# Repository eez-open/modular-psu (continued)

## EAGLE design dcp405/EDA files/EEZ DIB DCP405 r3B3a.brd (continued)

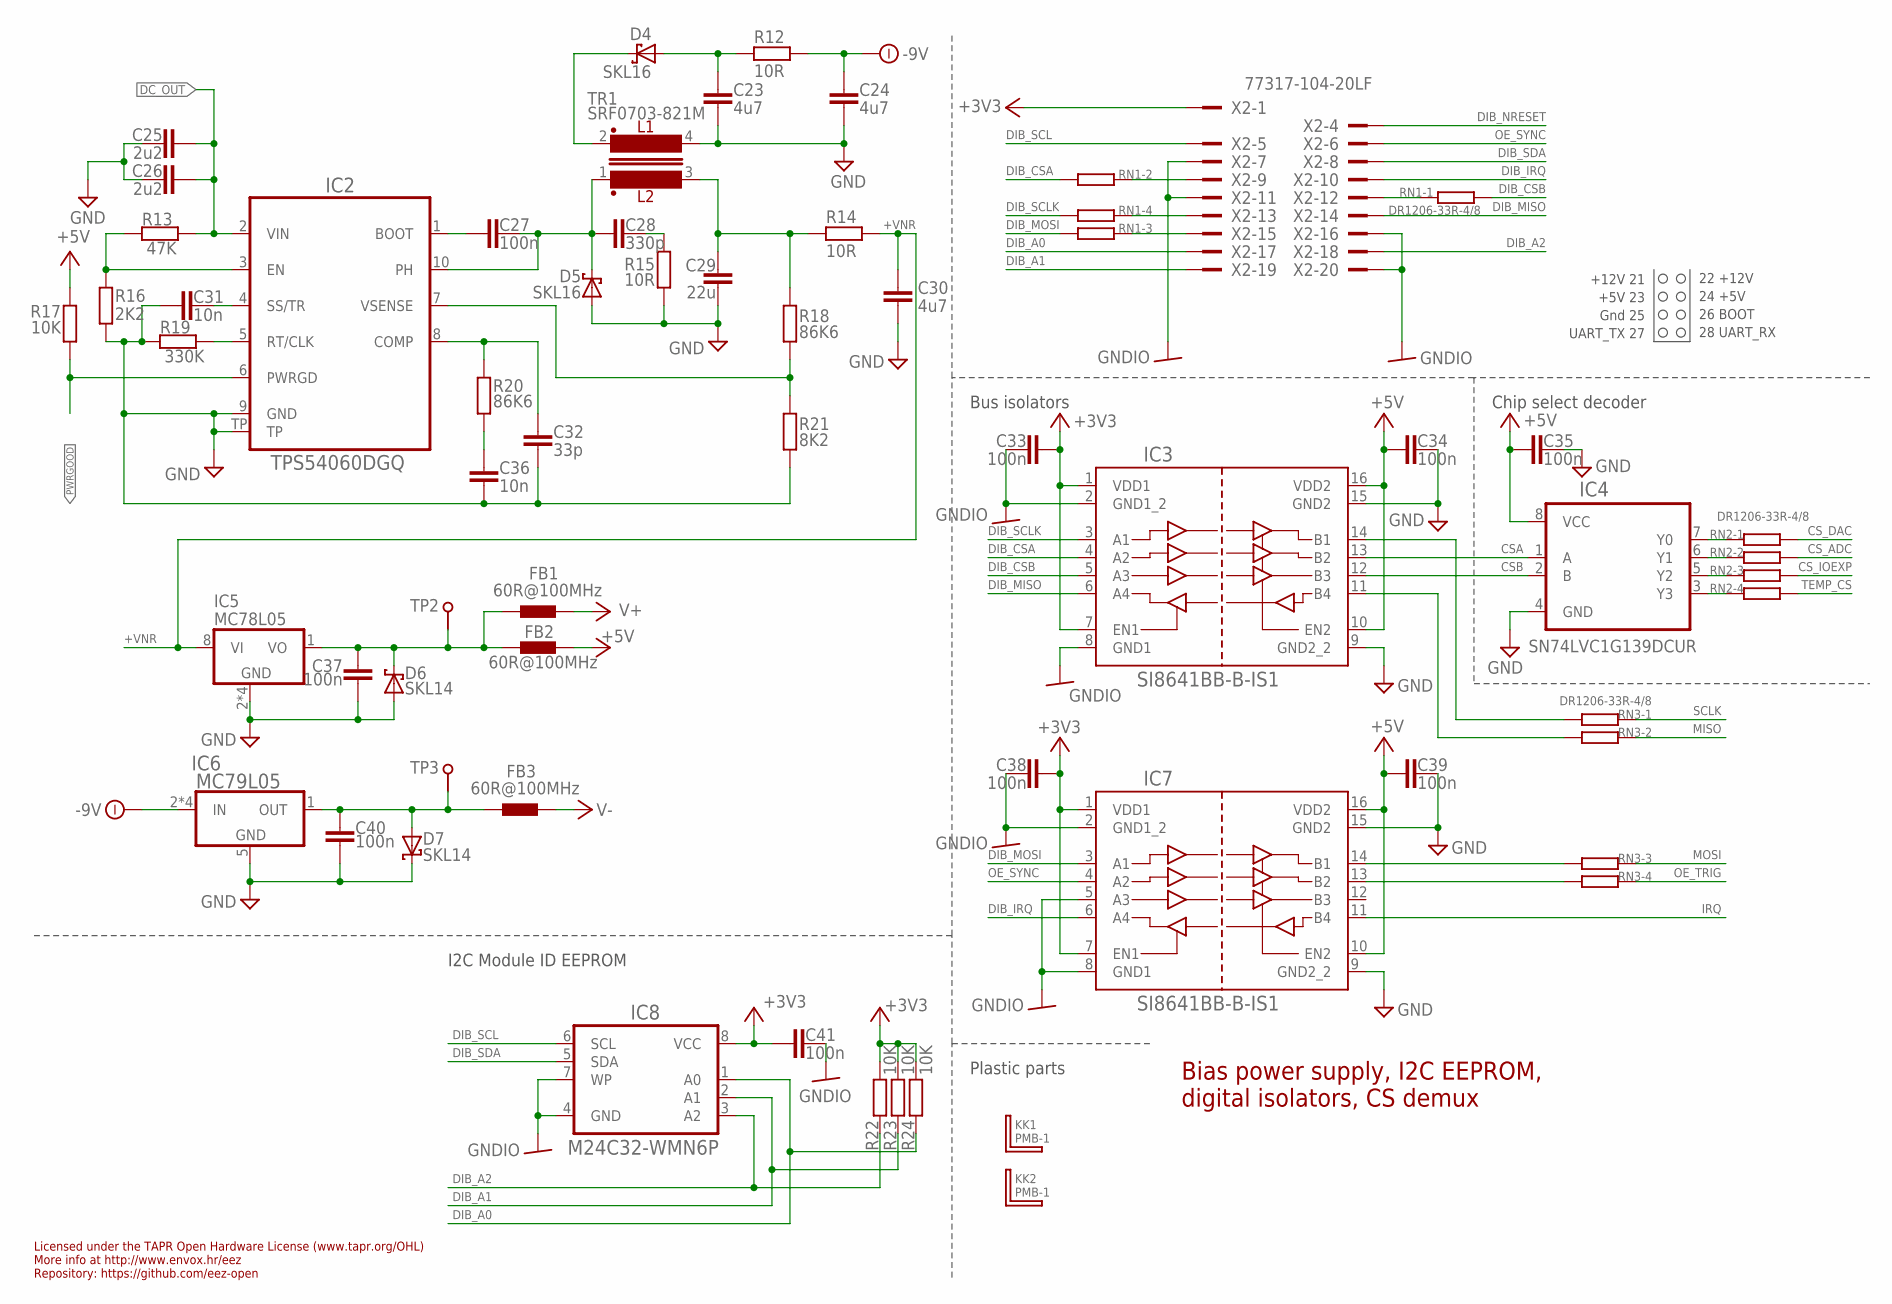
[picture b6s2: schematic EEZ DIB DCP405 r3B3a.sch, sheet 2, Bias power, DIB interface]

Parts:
C23, C24, C30: 4u7; C1206
C25, C26: 2u2; C1206
C27, C33, C34, C35, C37, C38, C39, C40, C41: 100n; C0603
C28: 330p; C0805
C29: 22u; C1210
C31, C36: 10n; C0805
C32: 33p; C0805
D4, D5: SKL16; SOD123
D6, D7: SKL14; SOD123
FB1, FB2, FB3: 60R@100MHz; BEAD0603
IC2: TPS54060DGQ; SOP50P490X110-11N
IC3, IC7: SI8641BB-B-IS1; SOIC-16
IC4: SN74LVC1G139DCUR; DCU8
IC5: MC78L05; SOIC127P600X173-8N
IC6: MC79L05; SOIC127P600X173-8N
IC8: M24C32-WMN6P; SOIC127P600X173-8N
KK1, KK2: PMB-1; PCB-MB
R12, R14, R15: 10R; R1206
R13: 47K; R0805
R16: 2K2; R0805
R17, R22, R23, R24: 10K; R0805
R18, R20: 86K6; R0805
R19: 330K; R0805
R21: 8K2; R0805
RN1, RN2, RN3: DR1206-33R-4/8; CAY16
TP2, TP3: TEST-PIN_0.9MM
TR1: SRF0703-821M; SRF0703
X2: 77317-104-20LF

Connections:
+3V3: C33.1, C38.1, C41.2, IC3.1 (VDD1), IC3.7 (EN1), IC7.1 (VDD1), IC7.7 (EN1), IC8.8 (VCC), R22.1, R23.1, R24.1, X2.1
+5V: C34.2, C35.1, C39.2, FB2.P$2 (2), IC3.10 (EN2), IC3.16 (VDD2), IC4.8 (VCC), IC7.10 (EN2), IC7.16 (VDD2), R17.1; also elsewhere on the board
+5VOUT: C37.1, D6.C, FB1.P$1 (1), FB2.P$1 (1), IC5.1 (VO), TP2.1
+VNR: C30.1, IC5.8 (VI), R14.1; also elsewhere on the board
-9V: C24.1, IC6.2 (IN), IC6.3 (IN), IC6.6 (IN), IC6.7 (IN), R12.1; also elsewhere on the board
CSA: IC3.13 (B2), IC4.1 (A)
CSB: IC3.12 (B3), IC4.2 (B)
CS_ADC: RN2.7 (2); also elsewhere on the board
CS_DAC: RN2.8 (2); also elsewhere on the board
CS_IOEXP: RN2.6 (2); also elsewhere on the board
DC_OUT: C25.1, C26.1, IC2.2 (VIN), R13.2; also elsewhere on the board
DIB_A0: IC8.1 (A0), R24.2, X2.17
DIB_A1: IC8.2 (A1), R23.2, X2.19
DIB_A2: IC8.3 (A2), R22.2, X2.18
DIB_CSA: IC3.4 (A2), RN1.2 (1)
DIB_CSB: IC3.5 (A3), RN1.1
DIB_IRQ: IC7.6 (A4), X2.10
DIB_MISO: IC3.6 (A4), X2.14
DIB_MOSI: IC7.3 (A1), RN1.3 (1)
DIB_NRESET: X2.4
DIB_SCL: IC8.6 (SCL), X2.5
DIB_SCLK: IC3.3 (A1), RN1.4 (1)
DIB_SDA: IC8.5 (SDA), X2.8
GND: C23.2, C24.2, C25.2, C26.2, C29.2, C30.2, C31.2, C32.1, C34.1, C35.2, C36.1, C37.2, C39.1, C40.1, D5.A, D6.A, D7.C, IC2.9 (GND), IC2.TP, IC3.9 (GND2_2), IC3.15 (GND2), IC4.4 (GND), IC5.2 (GND), IC5.3 (GND), IC5.6 (GND), IC5.7 (GND), IC6.5 (GND), IC7.9 (GND2_2), IC7.15 (GND2), R15.1, R16.1, R19.1, R21.1, TR1.4; also elsewhere on the board
GNDIO: C33.2, C38.2, C41.1, IC3.2 (GND1_2), IC3.8 (GND1), IC7.2 (GND1_2), IC7.5 (A3), IC7.8 (GND1), IC8.4 (GND), IC8.7 (WP), X2.7, X2.11, X2.16, X2.20
IRQ: IC7.11 (B4); also elsewhere on the board
MISO: RN3.7 (2); also elsewhere on the board
MOSI: RN3.6 (2); also elsewhere on the board
unnamed: IC7.13 (B2), RN3.4 (1)
unnamed: IC4.5 (Y2), RN2.3 (1)
unnamed: IC4.7 (Y0), RN2.1
unnamed: IC3.11 (B4), RN3.2 (1)
unnamed: RN1.7 (2), X2.9
unnamed: IC4.6 (Y1), RN2.2 (1)
unnamed: RN1.5 (2), X2.13
unnamed: C28.2, R15.2
unnamed: RN1.6 (2), X2.15
unnamed: C40.2, D7.A, FB3.P$1 (1), IC6.1 (OUT), TP3.1
unnamed: RN1.8 (2), X2.12
unnamed: IC2.3 (EN), R13.1, R16.2
unnamed: C31.1, IC2.4 (SS/TR)
unnamed: IC2.5 (RT/CLK), R19.2
unnamed: C32.2, IC2.8 (COMP), R20.2
unnamed: C36.2, R20.1
unnamed: IC4.3 (Y3), RN2.4 (1)
unnamed: C27.2, IC2.1 (BOOT)
unnamed: IC7.14 (B1), RN3.3 (1)
unnamed: IC2.7 (VSENSE), R18.1, R21.2
unnamed: IC3.14 (B1), RN3.1
unnamed: C23.1, D4.A, R12.2
OE_SYNC: IC7.4 (A2), X2.6
OE_TRIG: RN3.5 (2); also elsewhere on the board
PH: C27.1, C28.1, D5.C, IC2.10 (PH), TR1.1
PWRGOOD: IC2.6 (PWRGD), R17.2; also elsewhere on the board
SCLK: RN3.8 (2); also elsewhere on the board
TEMP_CS: RN2.5 (2); also elsewhere on the board
V+: FB1.P$2 (2); also elsewhere on the board
V-: FB3.P$2 (2); also elsewhere on the board
VOUT+: C29.1, R14.2, R18.2, TR1.3
VOUT-: D4.C, TR1.2

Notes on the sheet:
Licensed under the TAPR Open Hardware License (www.tapr.org/OHL)
Repository: https://github.com/eez-open
More info at http://www.envox.hr/eez
I2C Module ID EEPROM
Bus isolators
Bias power supply, I2C EEPROM, digital isolators, CS demux
Plastic parts
Chip select decoder
22 +12V
24 +5V
+5V 23
Gnd 25
+12V 21
26 BOOT
UART_TX 27
28 UART_RX

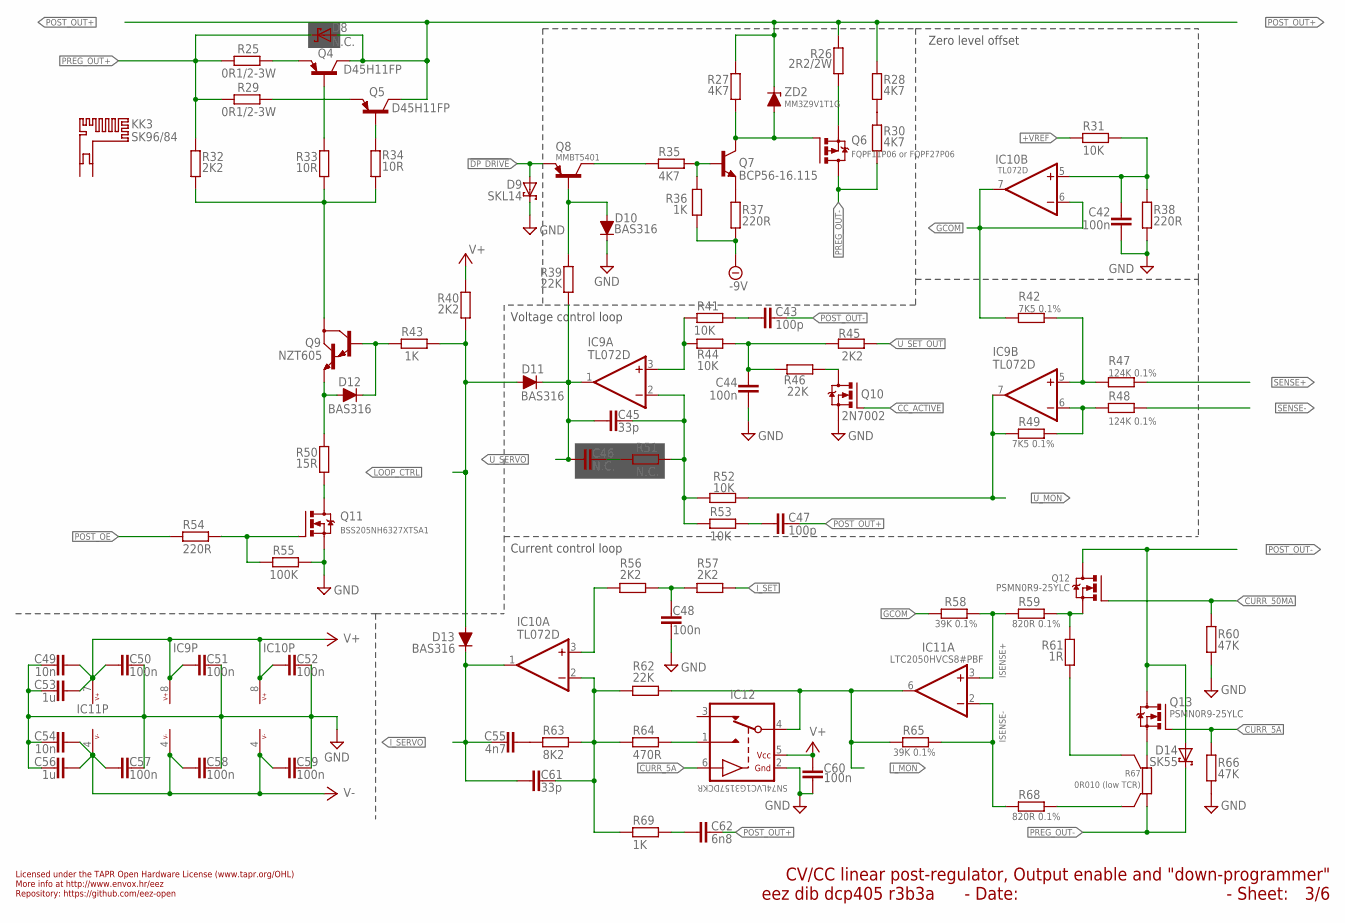
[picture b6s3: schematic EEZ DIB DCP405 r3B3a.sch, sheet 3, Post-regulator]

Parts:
C42, C44, C48, C50, C51, C52, C57, C58, C59, C60: 100n; C0603
C43, C47: 100p; C0805
C45, C61: 33p; C0805
C46: N.C.; C0805
C49, C54: 10n; C0805
C53, C56: 1u; C0805
C55: 4n7; C0805
C62: 6n8; C0805
D8: N.C.; SOD123
D9: SKL14; SOD123
D10, D11, D12, D13: BAS316; SOD323-R
D14: SK55; SMB
IC9, IC10: TL072D; SOIC127P600X173-8N
IC11: LTC2050HVCS8#PBF; SOIC127P600X173-8N
IC12: SN74LVC1G3157DCKR; SOT65P210X110-6N
KK3: SK96/84
Q4, Q5: D45H11FP; TO220FP-V
Q6: FQPF11P06 or FQPF27P06; TO220FP-V
Q7: BCP56-16.115; SOT230P700X180-4N
Q8: MMBT5401; SOT23-BEC
Q9: NZT605; SOT230P700X180-4N
Q10: 2N7002; SOT103P240X110-3N
Q11: BSS205NH6327XTSA1; SOT103P240X110-3N; MPN 2N7002-7-F
Q12, Q13: PSMN0R9-25YLC; SOT669
R25, R29: 0R1/2-3W; R2512
R26: 2R2/2W; R2512
R27, R28, R30, R35: 4K7; R0805
R31, R41, R44, R52, R53: 10K; R0805
R32, R40, R45, R56, R57: 2K2; R0805
R33, R34: 10R; R1206
R36, R43, R69: 1K; R0805
R37, R38, R54: 220R; R0805
R39, R46, R62: 22K; R0805
R42, R49: 7K5 0.1%; R0805
R47, R48: 124K 0.1%; R0805
R50: 15R; R2010
R51: N.C.; R0805
R55: 100K; R0805
R58, R65: 39K 0.1%; R0805
R59, R68: 820R 0.1%; R0805
R60, R66: 47K; R0805
R61: 1R; R1206
R63: 8K2; R0805
R64: 470R; R0805
R67: 0R010 (low TCR); R_2512-4WIRE
ZD2: MM3Z9V1T1G; SOD323-R

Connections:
5A_S: Q13.1 (S), Q13.2 (S), Q13.3 (S), R67.2
50MA_S: Q12.1 (S), Q12.2 (S), Q12.3 (S), R59.1, R61.1
!DP_DRIVE: D9.A, Q8.E; also elsewhere on the board
+VREF: R31.1; also elsewhere on the board
-9V: R36.2, R37.2; also elsewhere on the board
CC_ACTIVE: Q10.1 (G); also elsewhere on the board
CURR_5A: IC12.6 (CTRL), Q13.4 (G), R66.2; also elsewhere on the board
CURR_50MA: Q12.4 (G), R60.2; also elsewhere on the board
DARL_C1: Q9.2 (C), Q9.4 (C), R32.1, R33.1, R34.1
DP_S: Q6.3 (S), R26.1
GCOM: IC10.6 (-IN), IC10.7 (OUT), R42.1, R58.1
GND: C42.2, C44.2, C48.2, C49.1, C50.2, C51.1, C52.1, C53.1, C54.1, C56.1, C57.2, C58.1, C59.1, C60.2, D9.C, D10.C, IC12.2 (GND), Q10.2 (S), Q11.2 (S), R38.2, R55.1, R60.1, R66.1; also elsewhere on the board
ISENSE+: IC11.3 (+IN), R58.2, R59.2
ISENSE-: IC11.2 (-IN), R65.1, R68.2
I_MON: IC11.6 (OUT), IC12.4 (COM), R62.1, R65.2; also elsewhere on the board
I_SERVO: C55.2, C61.2, D13.C, IC10.1 (OUT); also elsewhere on the board
I_SET: R57.1; also elsewhere on the board
LOOP_CTRL: D11.A, D13.A, R40.1, R43.1; also elsewhere on the board
unnamed: Q10.3 (D), R46.1
unnamed: C48.1, R56.1, R57.2
unnamed: R61.2, R67.2S
unnamed: C46.1, R51.2
unnamed: C55.1, R63.1
unnamed: Q5.1 (B), R34.2
unnamed: IC12.1 (NO), R64.1
unnamed: IC10.3 (+IN), R56.2
unnamed: IC9.3 (+IN), R41.2, R44.2
unnamed: C45.1, IC9.2 (-IN), R51.1, R52.2, R53.2
unnamed: Q4.1 (B), R33.2
unnamed: D12.A, Q9.3 (E), R50.2
unnamed: Q11.3 (D), R50.1
unnamed: C62.2, R69.1
unnamed: C61.1, IC10.2 (-IN), R62.2, R63.2, R64.2, R69.2
unnamed: C43.2, R41.1
unnamed: C47.2, R53.1
unnamed: R28.1, R30.2
unnamed: Q7.1 (B), R35.1, R36.1
unnamed: Q8.C, R35.2
unnamed: D10.A, Q8.B, R39.2
unnamed: Q11.1 (G), R54.1, R55.2
unnamed: Q7.3 (E), R37.1
unnamed: D12.C, Q9.1 (B), R43.2
unnamed: C42.1, IC10.5 (+IN), R31.2, R38.1
unnamed: IC9.5 (+IN), R42.2, R47.1
unnamed: IC9.6 (-IN), R48.1, R49.2
unnamed: R67.1S, R68.1
PASS_E1: Q4.3 (E), R25.2
PASS_E2: Q5.3 (E), R29.2
POST_OE: R54.2; also elsewhere on the board
POST_OUT+: C47.1, C62.1, D8.A, Q4.2 (C), Q5.2 (C), R26.2, R27.1, R28.2, ZD2.C; also elsewhere on the board
POST_OUT-: C43.1, D14.A, Q12.MB (D), Q13.MB (D); also elsewhere on the board
PREG_OUT+: D8.C, R25.1, R29.1, R32.2; also elsewhere on the board
PREG_OUT-: D14.C, Q6.2 (D), R30.1, R67.1; also elsewhere on the board
Q7C: Q6.1 (G), Q7.2 (C), Q7.4 (C), R27.2, ZD2.A
SENSE+: R47.2; also elsewhere on the board
SENSE-: R48.2; also elsewhere on the board
U_MON: IC9.7 (OUT), R49.1, R52.1; also elsewhere on the board
U_SERVO: C45.2, C46.2, D11.C, IC9.1 (OUT), R39.1; also elsewhere on the board
U_SET_OUT: R45.1; also elsewhere on the board
U_SET_OVP: C44.1, R44.1, R45.2, R46.2
V+: C49.2, C50.1, C51.2, C52.2, C53.2, C60.1, IC9.8 (V+), IC10.8 (V+), IC11.7 (V+), IC12.5 (VDD), R40.2; also elsewhere on the board
V-: C54.2, C56.2, C57.1, C58.2, C59.2, IC9.4 (V-), IC10.4 (V-), IC11.4 (V-); also elsewhere on the board

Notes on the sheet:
Voltage control loop
Licensed under the TAPR Open Hardware License (www.tapr.org/OHL)
Repository: https://github.com/eez-open
More info at http://www.envox.hr/eez
Zero level offset
CV/CC linear post-regulator, Output enable and "down-programmer"
- Sheet:
- Date:
Current control loop

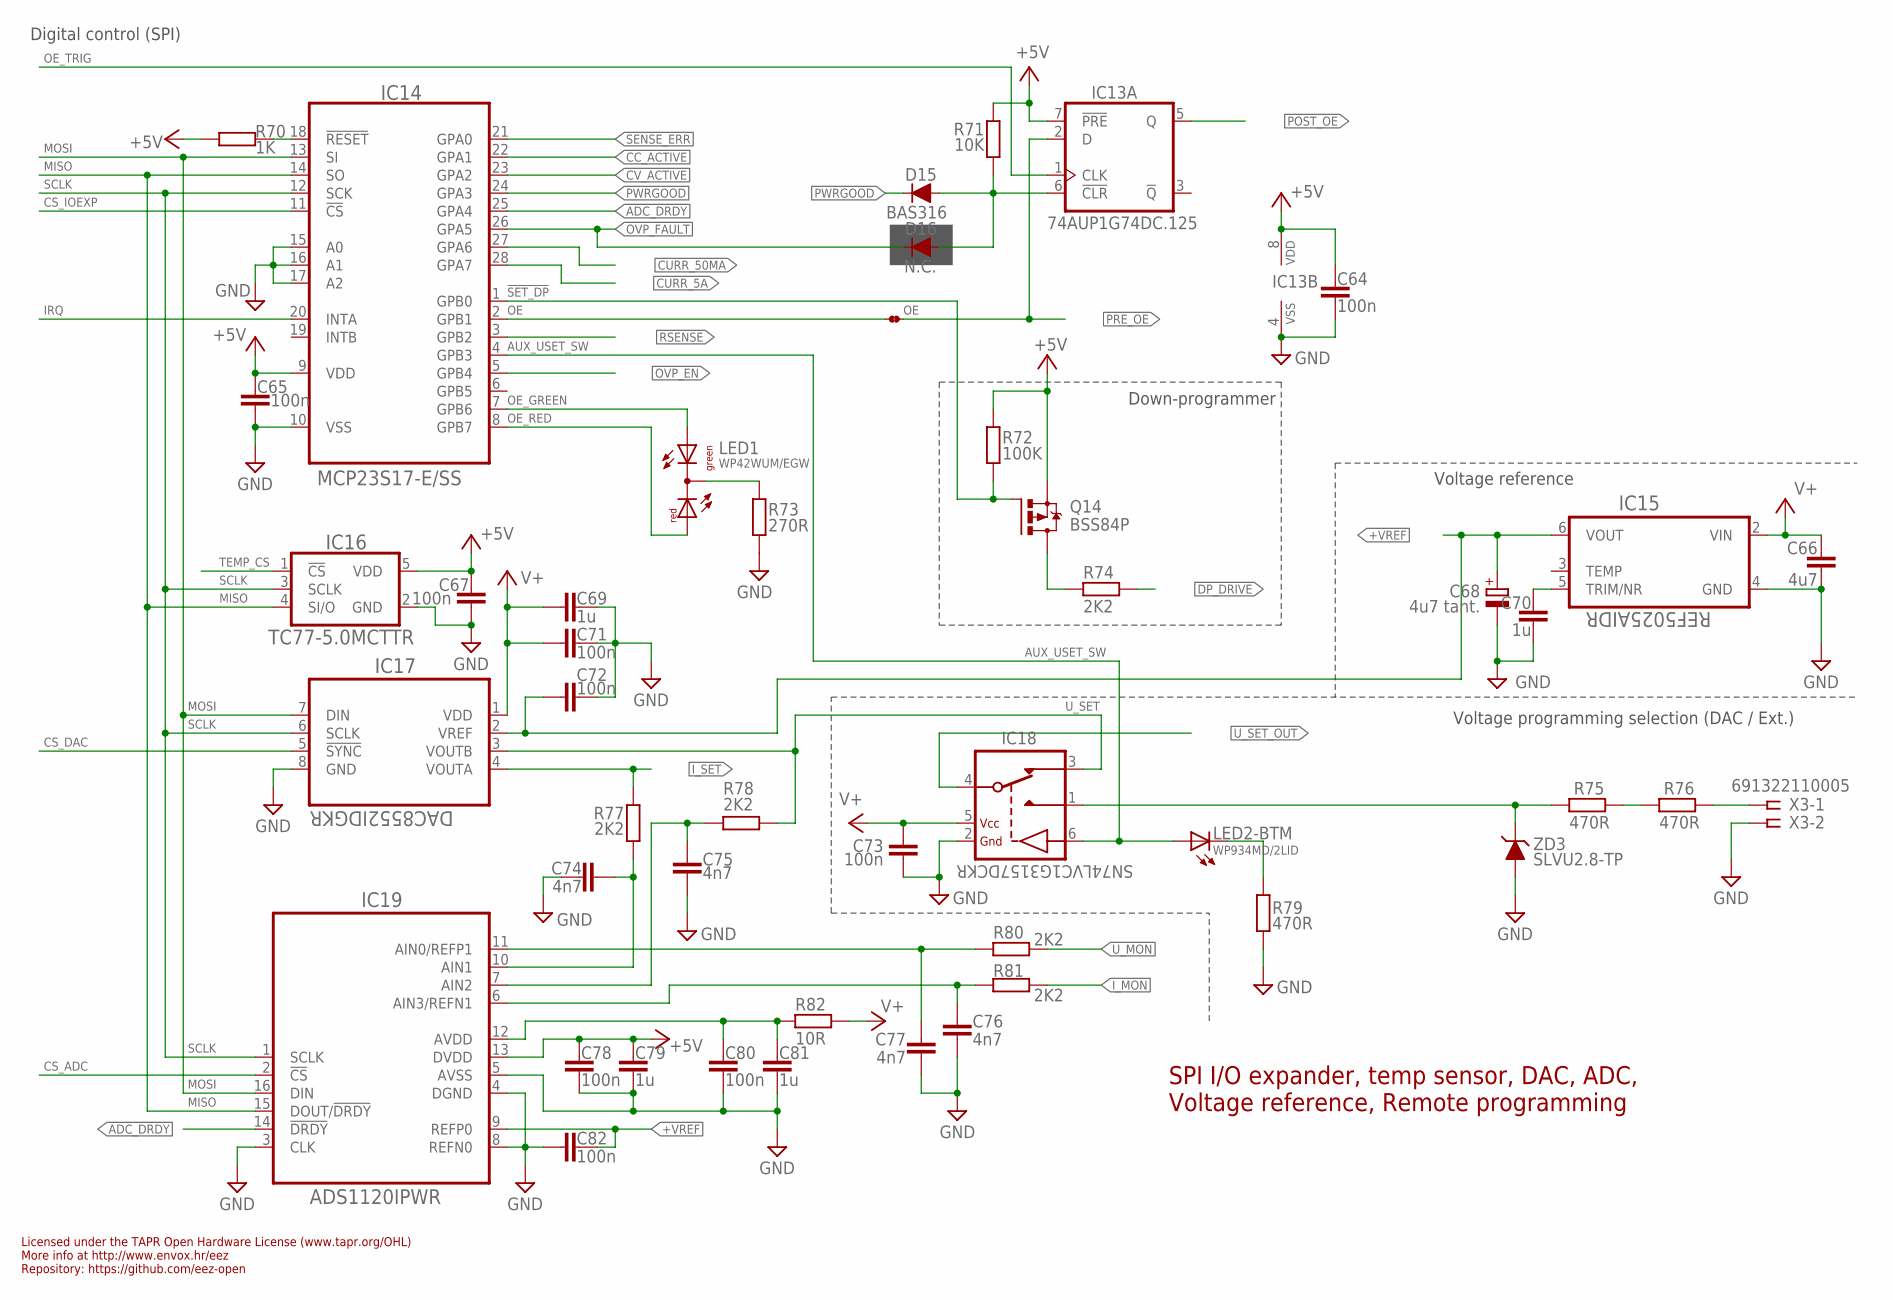
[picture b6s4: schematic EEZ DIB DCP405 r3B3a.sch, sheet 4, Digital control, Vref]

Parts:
C64, C65, C67, C71, C72, C73, C78, C80, C82: 100n; C0603
C66: 4u7; C1206
C68: 4u7 tant.; EC1206
C69, C70, C79, C81: 1u; C0805
C74, C75, C76, C77: 4n7; C0805
D15: BAS316; SOD323-R
D16: N.C.; SOD323-R
IC13: 74AUP1G74DC.125; DCU8
IC14: MCP23S17-E/SS; SOP65P780X200-28N
IC15: REF5025AIDR; SOIC127P600X175-8N
IC16: TC77-5.0MCTTR; SOT23-5
IC17: DAC8552IDGKR; DGK8-M
IC18: SN74LVC1G3157DCKR; SOT65P210X110-6N
IC19: ADS1120IPWR; PW(R-PDSO-G16)
LED1: WP42WUM/EGW; L-42WUM-1EGWT
LED2: WP934MD/2LID; WP934MD
OE: JP2-NOCUT
Q14: BSS84P; SOT95P237X112-3N
R70: 1K; R0805
R71: 10K; R0805
R72: 100K; R0805
R73: 270R; R0805
R74, R77, R78, R80, R81: 2K2; R0805
R75, R76, R79: 470R; R0805
R82: 10R; R1206
X3: 691322110005; MC1,5/5-G-3,5
ZD3: SLVU2.8-TP; SOT23

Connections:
!ADC_DRDY: IC14.25 (GPA4), IC19.14 (!DRDY)
!DP_DRIVE: R74.1; also elsewhere on the board
!IOEXP_RST: IC14.18 (!RESET), R70.2
!OVP_FAULT: D16.C, IC14.26 (GPA5); also elsewhere on the board
!SET_DP: IC14.1 (GPB0), Q14.1 (G), R72.2
+5V: C64.2, C65.1, C67.1, C78.2, C79.2, IC13.7 (!PRE), IC13.8 (VDD), IC14.9 (VDD), IC16.5 (VDD), IC19.13 (DVDD), Q14.2 (S), R70.1, R71.1, R72.1; also elsewhere on the board
+VREF: C68.+, C72.2, C82.2, IC15.6 (VOUT), IC17.2 (VREF), IC19.9 (REFP0); also elsewhere on the board
AUX_IN: IC18.1 (NO), R75.1, ZD3.3 (C)
AUX_USET_SW: IC14.4 (GPB3), IC18.6 (CTRL), LED2.BA (A)
CC_ACTIVE: IC14.22 (GPA1); also elsewhere on the board
CS_ADC: IC19.2 (!CS); also elsewhere on the board
CS_DAC: IC17.5 (!SYNC); also elsewhere on the board
CS_IOEXP: IC14.11 (!CS); also elsewhere on the board
CURR_5A: IC14.28 (GPA7); also elsewhere on the board
CURR_50MA: IC14.27 (GPA6); also elsewhere on the board
CV_ACTIVE: IC14.23 (GPA2); also elsewhere on the board
GND: C64.1, C65.2, C66.2, C67.2, C68.-, C69.2, C70.2, C71.1, C72.1, C73.2, C74.1, C75.1, C76.2, C77.1, C78.1, C79.1, C80.1, C81.1, C82.1, IC13.4 (VSS), IC14.10 (VSS), IC14.15 (A0), IC14.16 (A1), IC14.17 (A2), IC15.4 (GND), IC16.2 (GND), IC17.8 (GND), IC18.2 (GND), IC19.3 (CLK), IC19.4 (DGND), IC19.5 (AVSS), IC19.8 (REFN0), R73.2, R79.1, X3.2, ZD3.1 (A), ZD3.2 (A); also elsewhere on the board
IRQ: IC14.20 (INTA); also elsewhere on the board
I_MON: R81.1; also elsewhere on the board
I_SET: IC17.4 (VOUTA), R77.1; also elsewhere on the board
MISO: IC14.14 (SO), IC16.4 (SI/O), IC19.15 (DOUT/!DRDY); also elsewhere on the board
MOSI: IC14.13 (SI), IC17.7 (DIN), IC19.16 (DIN); also elsewhere on the board
unnamed: LED1.CC (C), R73.1
unnamed: R75.2, R76.1
unnamed: R76.2, X3.1
unnamed: Q14.3 (D), R74.2
unnamed: D15.A, D16.A, IC13.6 (!CLR), R71.2
unnamed: C80.2, C81.2, IC19.12 (AVDD), R82.2
unnamed: C70.1, IC15.5 (TRIM/NR)
unnamed: C74.2, IC19.10 (AIN1), R77.2
unnamed: C77.2, IC19.11 (AIN0/REFP1), R80.2
unnamed: C75.2, IC19.7 (AIN2), R78.2
unnamed: C76.1, IC19.6 (AIN3/REFN1), R81.2
unnamed: LED2.BC (C), R79.2
OE: IC14.2 (GPB1), OE.1
OE_GREEN: IC14.7 (GPB6), LED1.GREEN (AG)
OE_RED: IC14.8 (GPB7), LED1.RED (AR)
OE_TRIG: IC13.1 (CLK); also elsewhere on the board
OVP_EN: IC14.5 (GPB4); also elsewhere on the board
POST_OE: IC13.5 (Q); also elsewhere on the board
PRE_OE: IC13.2 (D), OE.2; also elsewhere on the board
PWRGOOD: D15.C, IC14.24 (GPA3); also elsewhere on the board
RSENSE: IC14.3 (GPB2); also elsewhere on the board
SCLK: IC14.12 (SCK), IC16.3 (SCLK), IC17.6 (SCLK), IC19.1 (SCLK); also elsewhere on the board
SENSE_ERR: IC14.21 (GPA0); also elsewhere on the board
TEMP_CS: IC16.1 (!CS); also elsewhere on the board
U_MON: R80.1; also elsewhere on the board
U_SET: IC17.3 (VOUTB), IC18.3 (NC), R78.1
U_SET_OUT: IC18.4 (COM); also elsewhere on the board
V+: C66.1, C69.1, C71.2, C73.1, IC15.2 (VIN), IC17.1 (VDD), IC18.5 (VDD), R82.1; also elsewhere on the board

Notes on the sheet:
Digital control (SPI)
Voltage reference
Licensed under the TAPR Open Hardware License (www.tapr.org/OHL)
Repository: https://github.com/eez-open
More info at http://www.envox.hr/eez
SPI I/O expander, temp sensor, DAC, ADC, Voltage reference, Remote programming
Voltage programming selection (DAC / Ext.)
Down-programmer

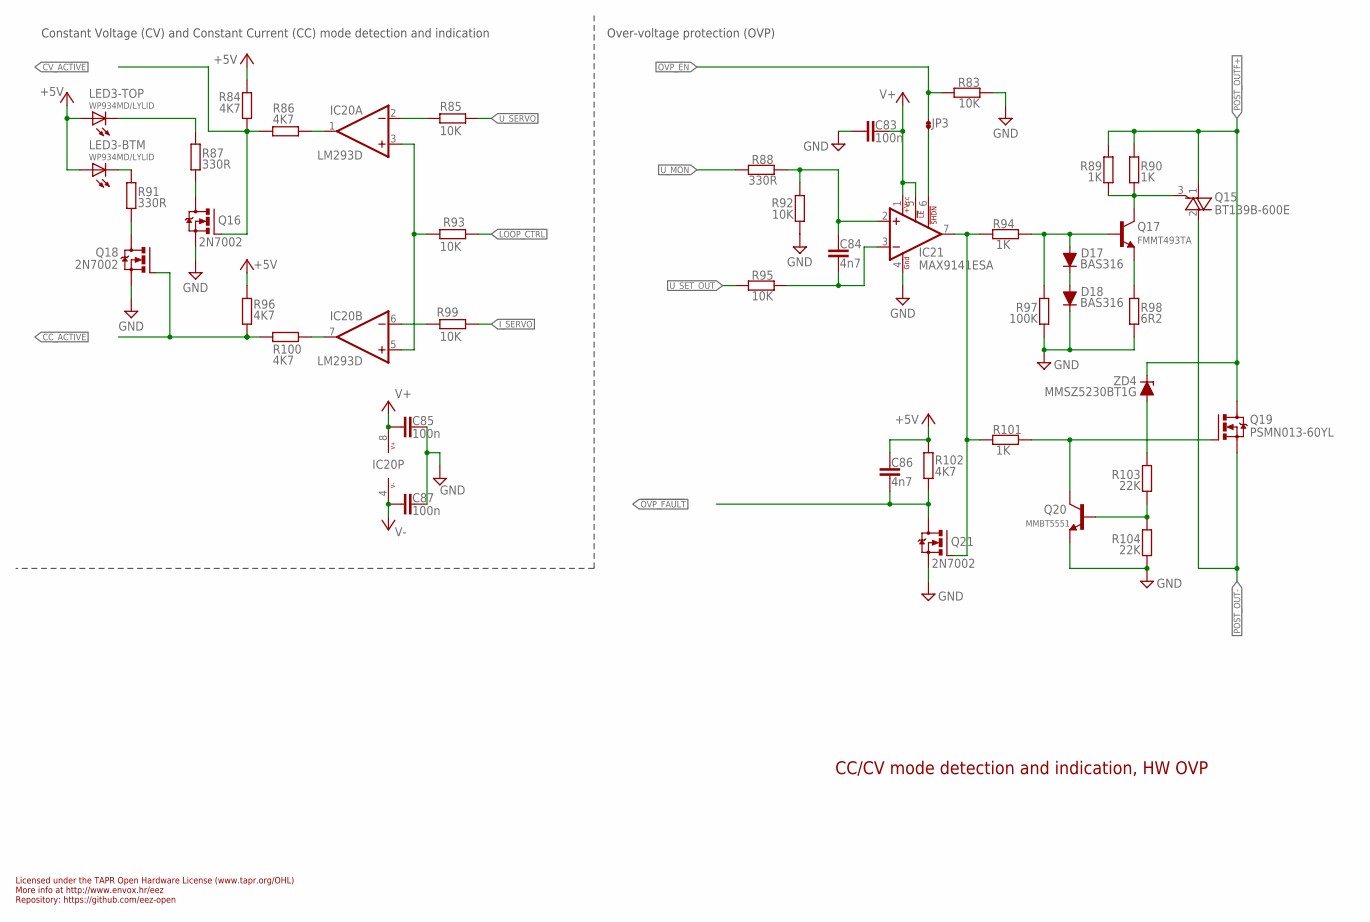
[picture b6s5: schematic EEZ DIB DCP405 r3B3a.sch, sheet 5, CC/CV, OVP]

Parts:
C83, C85, C87: 100n; C0603
C84, C86: 4n7; C0805
D17, D18: BAS316; SOD323-R
IC20: LM293D; SOIC127P600X173-8N
IC21: MAX9141ESA; SOIC127P600X173-8N
JP3: JP2-NOCUT-0805; JP2-0805-NOCUT
LED3: WP934MD/LYLID; WP934MD
Q15: BT139B-600E; D2PAK
Q16, Q18, Q21: 2N7002; SOT103P240X110-3N
Q17: FMMT493TA; SOT23-BEC
Q19: PSMN013-60YL; SOT669
Q20: MMBT5551; SOT23-BEC
R83, R85, R92, R93, R95, R99: 10K; R0805
R84, R86, R96, R100, R102: 4K7; R0805
R87, R88, R91: 330R; R0805
R89, R90, R94, R101: 1K; R0805
R97: 100K; R0805
R98: 6R2; R0805
R103, R104: 22K; R0805
ZD4: MMSZ5230BT1G; SOD123

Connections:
!OVP_FAULT: C86.2, Q21.3 (D), R102.2; also elsewhere on the board
+5V: C86.1, LED3.BA (A), LED3.TA (A), R84.2, R96.2, R102.1; also elsewhere on the board
CC_ACTIVE: Q18.1 (G), R96.1, R100.2; also elsewhere on the board
CC_LED: LED3.BC (C), R91.2
CV_ACTIVE: Q16.1 (G), R84.1, R86.2; also elsewhere on the board
CV_LED: LED3.TC (C), R87.1
D_CC: Q18.3 (D), R91.1
D_CV: Q16.3 (D), R87.2
GND: C83.1, C85.1, C87.1, D18.C, IC21.4 (GND), Q16.2 (S), Q18.2 (S), Q20.E, Q21.2 (S), R83.1, R92.2, R97.1, R98.1, R104.1; also elsewhere on the board
I_SERVO: R99.1; also elsewhere on the board
LOOP_CTRL: R93.2; also elsewhere on the board
unnamed: IC21.6 (!SHDN), JP3.2
unnamed: IC21.7 (OUT), Q21.1 (G), R94.2, R101.2
unnamed: Q15.3 (G), Q17.C, R89.1, R90.1
unnamed: Q17.E, R98.2
unnamed: D17.C, D18.A
unnamed: D17.A, Q17.B, R94.1, R97.2
unnamed: R103.2, ZD4.A
unnamed: Q20.B, R103.1, R104.2
unnamed: Q19.4 (G), Q20.C, R101.1
unnamed: IC20.1 (OUT), R86.1
unnamed: IC20.7 (OUT), R100.1
unnamed: IC20.2 (-IN), R85.2
unnamed: IC20.6 (-IN), R99.2
unnamed: IC20.3 (+IN), IC20.5 (+IN), R93.1
OVP_EN: JP3.1, R83.2; also elsewhere on the board
OVP_IN+: C84.1, IC21.2 (+IN), R88.2, R92.1
OVP_IN-: C84.2, IC21.3 (-IN), R95.2
POST_OUT-: Q15.2 (A2), Q19.1 (S), Q19.2 (S), Q19.3 (S); also elsewhere on the board
POST_OUTF+: Q15.1 (A1), Q19.MB (D), R89.2, R90.2, ZD4.C; also elsewhere on the board
U_MON: R88.1; also elsewhere on the board
U_SERVO: R85.1; also elsewhere on the board
U_SET_OUT: R95.1; also elsewhere on the board
V+: C83.2, C85.2, IC20.8 (V+), IC21.1 (+VCC), IC21.5 (!LE); also elsewhere on the board
V-: C87.2, IC20.4 (V-); also elsewhere on the board

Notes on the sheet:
Licensed under the TAPR Open Hardware License (www.tapr.org/OHL)
Repository: https://github.com/eez-open
More info at http://www.envox.hr/eez
CC/CV mode detection and indication, HW OVP
Constant Voltage (CV) and Constant Current (CC) mode detection and indication
Over-voltage protection (OVP)

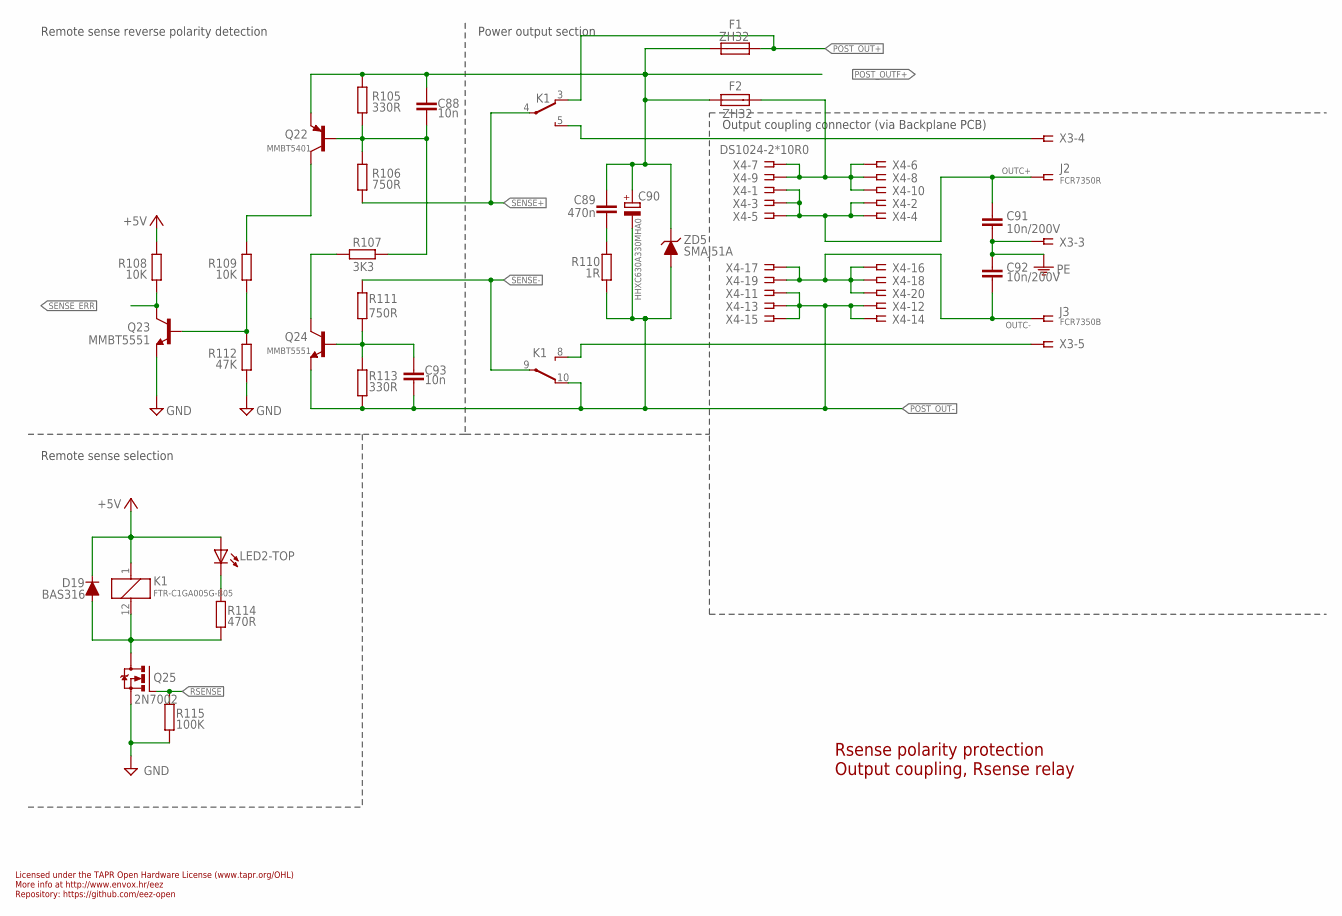
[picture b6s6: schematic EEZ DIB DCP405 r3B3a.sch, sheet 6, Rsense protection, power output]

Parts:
C88, C93: 10n; C0805
C89: 470n; C0805
C90: HHXC630A330MHA0; CAPAE830X1050N
C91, C92: 10n/200V; C1206
D19: BAS316; SOD323-R
F1, F2: ZH32
J2: FCR7350R; S16N-PC
J3: FCR7350B; S16N-PC
K1: FTR-C1GA005G-B05; FTR-C1
LED2: WP934MD/2LID; WP934MD
Q22: MMBT5401; SOT23-BEC
Q23, Q24: MMBT5551; SOT23-BEC
Q25: 2N7002; SOT103P240X110-3N
R105, R113: 330R; R0805
R106, R111: 750R; R0805
R107: 3K3; R0805
R108, R109: 10K; R0805
R110: 1R; R1206
R112: 47K; R0805
R114: 470R; R0805
R115: 100K; R0805
X3: 691322110005; MC1,5/5-G-3,5
X4: DS1024-2*10R0; SSW-110-02-T-D-RA
ZD5: SMAJ51A; DO214AA

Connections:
+5V: D19.C, K1.1 (C1), LED2.TA (A), R108.2; also elsewhere on the board
GND: Q23.E, Q25.2 (S), R112.1, R115.1; also elsewhere on the board
unnamed: C88.2, Q22.B, R105.1, R106.2, R107.2
unnamed: Q22.C, R109.2
unnamed: Q24.C, R107.1
unnamed: C93.1, Q24.B, R111.1, R113.2
unnamed: Q23.B, R109.1, R112.2
unnamed: C89.2, R110.2
unnamed: D19.A, K1.12 (C2), Q25.3 (D), R114.1
unnamed: K1.5 (O), X3.4
unnamed: K1.8 (O), X3.5
unnamed: LED2.TC (C), R114.2
OUTC+: C91.1, J2.1, X4.1, X4.2, X4.3, X4.4, X4.5
OUTC-: C92.2, J3.1, X4.16, X4.17, X4.18, X4.19, X4.20
OUTF+: F2.2, X4.6, X4.7, X4.8, X4.9, X4.10
PE: C91.2, C92.1, X3.3; also elsewhere on the board
POST_OUT+: F1.1, K1.3 (S); also elsewhere on the board
POST_OUT-: C90.-, C93.2, K1.10 (S), Q24.E, R110.1, R113.1, X4.11, X4.12, X4.13, X4.14, X4.15, ZD5.A; also elsewhere on the board
POST_OUTF+: C88.1, C89.1, C90.+, F1.2, F2.1, Q22.E, R105.2, ZD5.C; also elsewhere on the board
RSENSE: Q25.1 (G), R115.2; also elsewhere on the board
SENSE+: K1.4, R106.1; also elsewhere on the board
SENSE-: K1.9, R111.2; also elsewhere on the board
SENSE_ERR: Q23.C, R108.1; also elsewhere on the board

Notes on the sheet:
Rsense polarity protection Output coupling, Rsense relay
Licensed under the TAPR Open Hardware License (www.tapr.org/OHL)
Repository: https://github.com/eez-open
More info at http://www.envox.hr/eez
Remote sense reverse polarity detection
Remote sense selection
Output coupling connector (via Backplane PCB)
Power output section
